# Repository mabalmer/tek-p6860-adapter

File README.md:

# tek-p6860-adapter

This board is designed to take the Tektronix P6860 compression probe found on many Tektronix logic analyzers and break them out into 0.1" header. It includes a single 9-position SMD DIP switch so that you can individually choose to tie the grounds together to allow single-ended mode usage for the individual inputs. 

The Library folder contains a KiCad symbol and footprint for the probe pad layout.

The base schematic uses J-lead SMD DIP switches to save space, but there is an alternate set of gerber files for gull-wing lead DIP switches in the main directory. 

I've selected a set of wire-wrap style 0.1" header strips that go through the board, allowing you to use headers that have sockets as well as pins on the ones I've built myself. The Digi-Key part number for this is SAM1125-32-ND.

The matching gull-wing DIP switch part number is CT2199LPST-ND.

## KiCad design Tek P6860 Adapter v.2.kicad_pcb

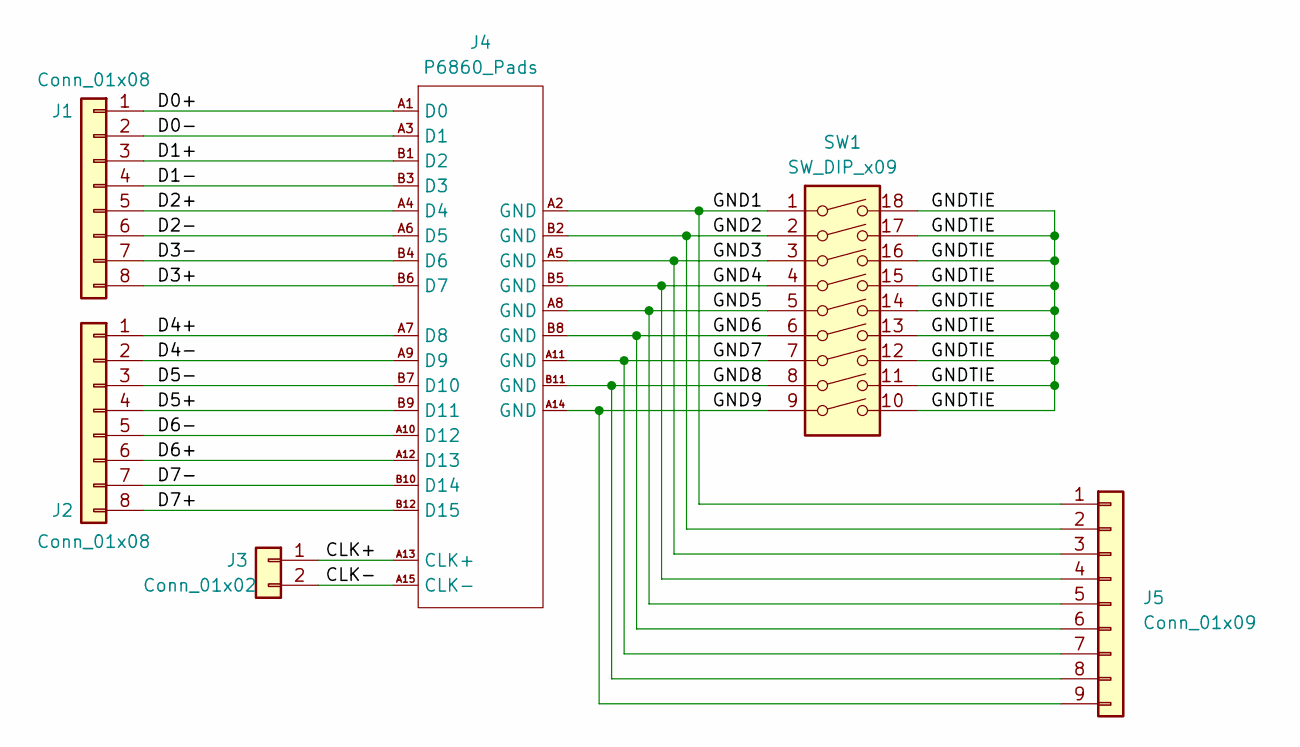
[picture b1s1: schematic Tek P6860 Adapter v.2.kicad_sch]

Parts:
J1, J2: Conn_01x08; PinHeader_1x08_P2.54mm_Vertical
J3: Conn_01x02; PinHeader_1x02_P2.54mm_Vertical
J4: P6860_Pads; Tek_6860_Footprint
J5: Conn_01x09; PinHeader_1x09_P2.54mm_Vertical
SW1: SW_DIP_x09; SW_DIP_SPSTx09_Slide_6.7x24.42mm_W6.73mm_P2.54mm_LowProfile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

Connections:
/CLK+: J3.1, J4.A13 (CLK+)
/CLK-: J3.2, J4.A15 (CLK-)
/D0+: J1.1, J4.A1 (D0)
/D0-: J1.2, J4.A3 (D1)
/D1+: J1.3, J4.B1 (D2)
/D1-: J1.4, J4.B3 (D3)
/D2+: J1.5, J4.A4 (D4)
/D2-: J1.6, J4.A6 (D5)
/D3+: J1.8, J4.B6 (D7)
/D3-: J1.7, J4.B4 (D6)
/D4+: J2.1, J4.A7 (D8)
/D4-: J2.2, J4.A9 (D9)
/D5+: J2.4, J4.B9 (D11)
/D5-: J2.3, J4.B7 (D10)
/D6+: J2.6, J4.A12 (D13)
/D6-: J2.5, J4.A10 (D12)
/D7+: J2.8, J4.B12 (D15)
/D7-: J2.7, J4.B10 (D14)
/GND1: J4.A2 (GND), J5.1, SW1.1
/GND2: J4.B2 (GND), J5.2, SW1.2
/GND3: J4.A5 (GND), J5.3, SW1.3
/GND4: J4.B5 (GND), J5.4, SW1.4
/GND5: J4.A8 (GND), J5.5, SW1.5
/GND6: J4.B8 (GND), J5.6, SW1.6
/GND7: J4.A11 (GND), J5.7, SW1.7
/GND8: J4.B11 (GND), J5.8, SW1.8
/GND9: J4.A14 (GND), J5.9, SW1.9
/GNDTIE: SW1.10, SW1.11, SW1.12, SW1.13, SW1.14, SW1.15, SW1.16, SW1.17, SW1.18

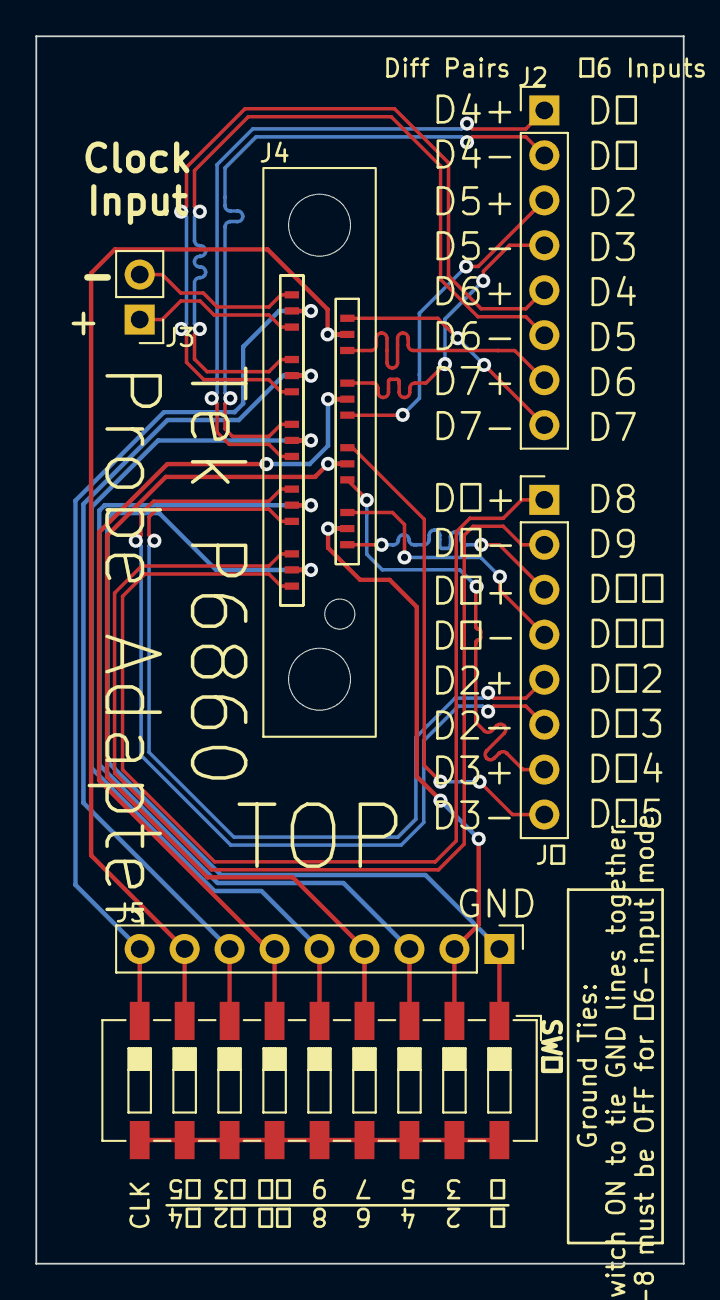
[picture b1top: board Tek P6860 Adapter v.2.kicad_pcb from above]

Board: 2 copper layers, 36.6 x 69.3 mm, 6 parts (0 on the bottom side), 28 nets.

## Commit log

2023-06-14 Add files via upload
    initial commit
2023-06-14 Add files via upload
    silkscreen fix
2023-06-14 add images
2023-06-28 Add gerbers for gull-wing lead DIP switches
2024-04-10 Add header/switch part numbers
